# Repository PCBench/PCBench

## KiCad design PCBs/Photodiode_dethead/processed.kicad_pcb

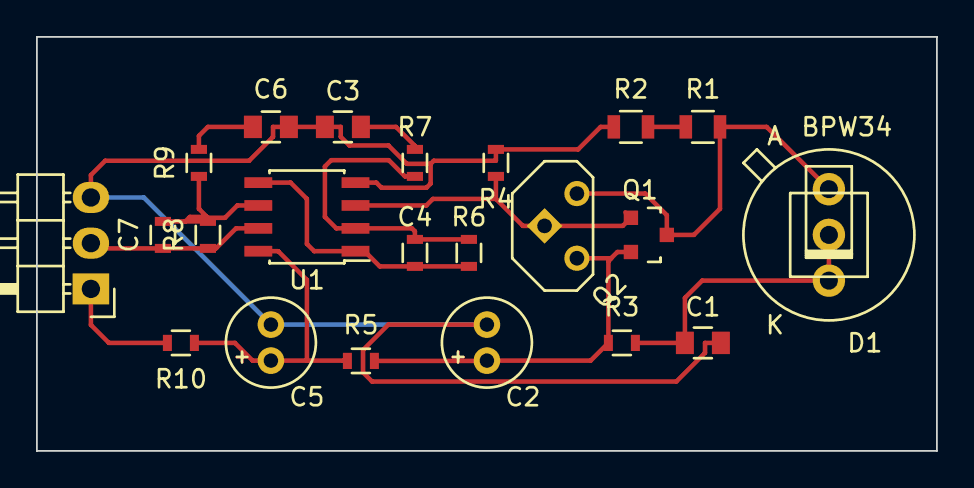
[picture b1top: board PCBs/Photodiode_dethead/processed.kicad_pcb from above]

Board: 2 copper layers, 50.0 x 23.0 mm, 22 parts (0 on the bottom side), 14 nets.

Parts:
C1, C3, C6: 100n; C_0805
C2, C5: 100u; Elko_vert_11x5mm_RM2
C4, C7: 47p; R_0603
D1: BPW34; PHOTODIODE_MULTI
P1: CONN_01X03; Pin_Header_Angled_1x03
Q1: BF545; SOT-23
Q2: FET_N; TO92GSD
R1, R2: 10M; R_0805
R3: 1M; R_0603
R4: 4k7; R_0603
R5: 1k; R_0603
R6, R8: 330k; R_0603
R7, R9: 10k; R_0603
R10: 100; R_0603
U1: LM358N; SOIC-8_3.9x4.9mm_Pitch1.27mm

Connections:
+BATT: P1.1, R10.1
/BIAS: C1.1, D1.2, R3.2
/DIODE_OUT: D1.1, Q1.3, Q2.G, R1.2
/SIG_OUT: C7.1, P1.2, R8.1, U1.7
GND: C1.2, C2.2, C3.2, C5.2, C6.2, P1.3, R2.1, R4.1, U1.4
unnamed: C2.1, Q1.2, Q2.D, R3.1, R5.2
unnamed: C3.1, R7.2
unnamed: C4.1, R6.1, U1.1, U1.5
unnamed: C4.2, R6.2, R7.1, U1.2
unnamed: C6.1, R9.2
unnamed: C7.2, R8.2, R9.1, U1.6
unnamed: Q1.1, Q2.S, R4.2, U1.3
unnamed: R1.1, R2.2
VCC: C5.1, R5.1, R10.2, U1.8

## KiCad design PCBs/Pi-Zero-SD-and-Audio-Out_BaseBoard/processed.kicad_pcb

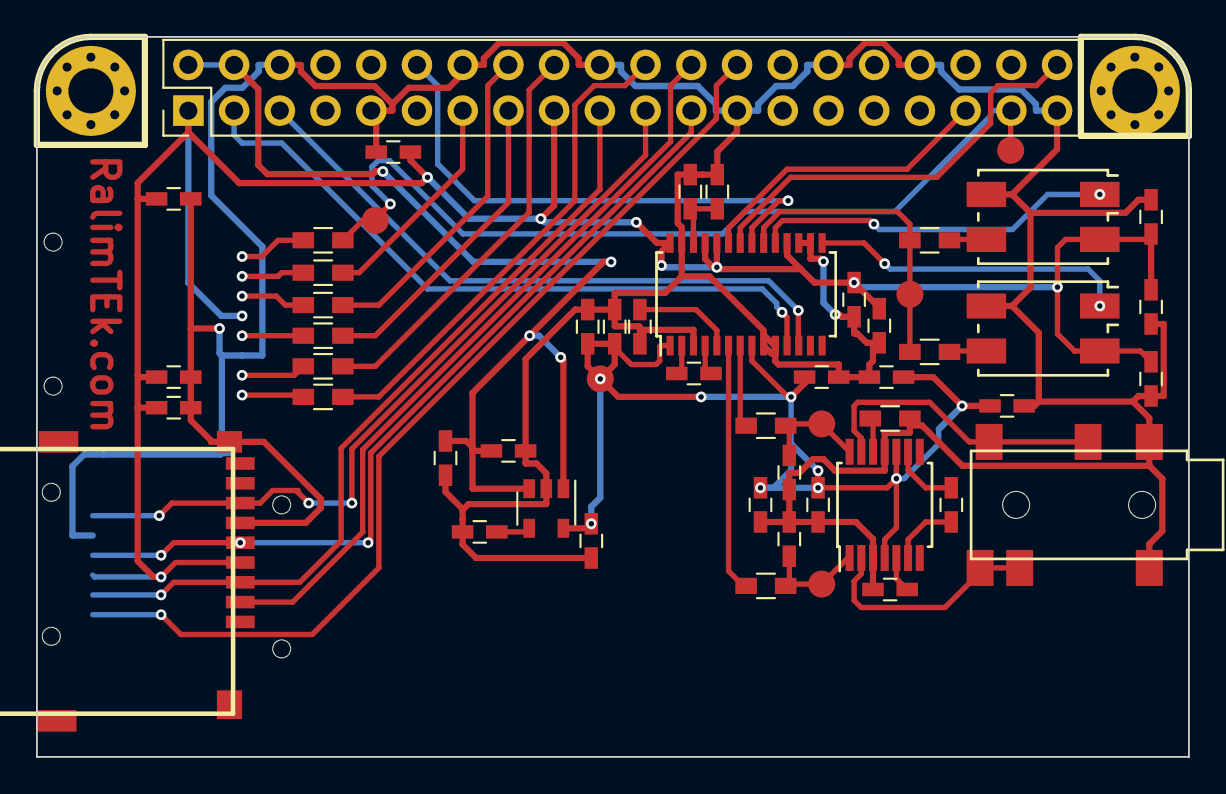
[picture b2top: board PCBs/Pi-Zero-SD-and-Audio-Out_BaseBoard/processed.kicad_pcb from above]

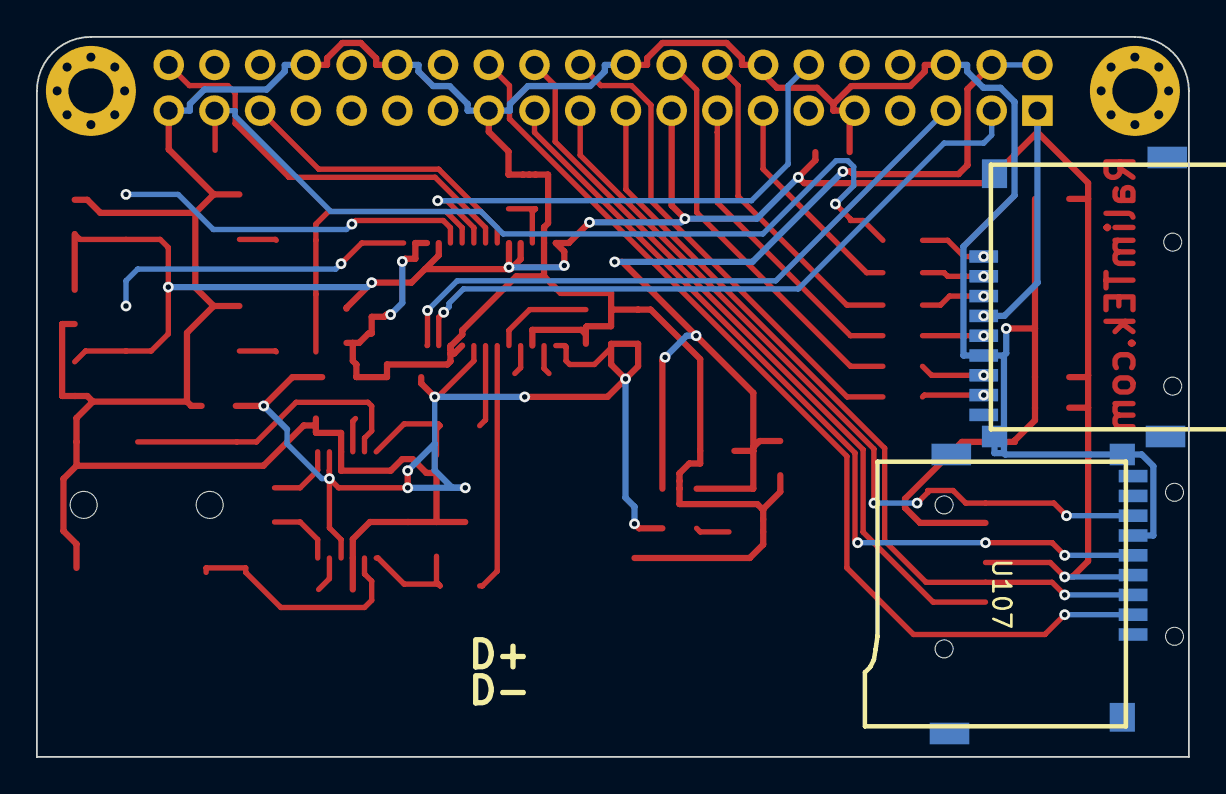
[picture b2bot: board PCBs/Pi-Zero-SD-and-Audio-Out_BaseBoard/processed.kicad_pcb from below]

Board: 2 copper layers, 64.0 x 40.0 mm, 57 parts (2 on the bottom side), 46 nets.

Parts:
C101, C102, C106, C107, C110, C111, C112, C113, C114, C115, C116, C117, C118, C119, C120, C121, C122, C123, C124, C125, C126, C127, C128: 0.1u; C_0603_HandSoldering
C103, C104, C105: 2.2uF; C_0603_HandSoldering
C108, C109: -; C_0603_HandSoldering
J101: RaspberryPi; Pin_Header_Straight_2x20_Pitch2.54mm
J102: JACK_TRS_6PINS; PJ311_6pin_3.5mm_SMD_Jack
P102, P104: CONN_01X01; MountingHole_2.5mm_Pad_Via
R101, R102, R103, R104, R107: 470; R_0603_HandSoldering
R105, R109: 33; R_0603_HandSoldering
R106, R108, R110, R111: 33R; R_0603_HandSoldering
U101: PCM5122; TSSOP-28_4.4x9.7mm_Pitch0.65mm
U103: TPA6139A2; TSSOP-14_4.4x5mm_Pitch0.65mm
U104: LD3985G; SOT-23-5
U105: Micro_SD_SDIO; GCT-MEM2055-00-190-01-A
U106, U107: MicroSD_SPI_CD; GCT-MEM2055-00-190-01-A
W101: CLK; Measurement_Point_Round-SMD-Pad_Small
W102: 3.3V; Measurement_Point_Round-SMD-Pad_Small
W103: L; Measurement_Point_Round-SMD-Pad_Small
W104: R; Measurement_Point_Round-SMD-Pad_Small
W108, W109: DAT2Link; Measurement_Point_Round-SMD-Pad_Small
X101: 24.576MHz; Crystal_SMD_7050_4Pads
X102: 22.5792MHz; Crystal_SMD_7050_4Pads

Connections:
/22MHZ_EN: U101.19, X102.1
/24MHZ_EN: U101.15, X101.1
/AVDD: C104.1, C111.1, C112.1, C113.1, C117.1, C119.1, C127.1, C128.1, U101.1, U101.8, U103.4, U103.10, U104.5, W102.1
/BCK: J101.12, U101.21
/CLK: J101.15, R105.2
/CMD: J101.16, R109.2
/DAC_L: C109.1, R101.2, U103.1, W103.1
/DAC_R: C108.2, R102.1, U103.14, W104.1
/DAT0: J101.18, R110.2
/DAT1: J101.22, R106.2
/DAT2: J101.37, R111.2, W108.1, W109.1
/DAT3: J101.13, R108.2
/DIN: J101.40, U101.22
/LRCLK: J101.35, U101.23
/MISO: J101.21, U106.7, U107.7
/MOSI: J101.19, U106.3, U107.3
/OUT_L: J102.4, J102.5, U103.2
/OUT_R: J102.3, J102.6, U103.13
/SCK: R103.2, R104.2, U101.20, W101.1
/SCL: J101.5, U101.12
/SCLK: J101.23, U106.5, U107.5
/SDA: J101.3, U101.11
/VBATT: C118.1, C120.1, J101.2, J101.4, U104.1, U104.3
/~CE0: J101.24, U106.2
/~CE1: J101.26, U107.2
GND: C101.2, C102.2, C104.2, C105.1, C106.2, C108.1, C109.2, C110.2, C111.2, C112.2, C113.2, C114.2, C115.2, C116.2, C117.2, C118.2, C119.2, C120.2, C121.2, C122.2, C123.2, C124.2, C125.2, C126.2, C127.2, C128.2, J101.6, J101.9, J101.14, J101.20, J101.25, J101.30, J101.34, J101.39, J102.1, J102.2, R107.2, U101.3, U101.9, U101.10, U101.16, U101.17, U101.27, U103.3, U103.11, U104.2, U105.6, U105.10, U106.6, U106.10, U107.6, U107.10, X101.2, X102.2
unnamed: C101.1, C102.1, U101.26
unnamed: C103.1, U101.2
unnamed: C103.2, U101.4
unnamed: C105.2, U101.5
unnamed: C106.1, U103.5
unnamed: C107.1, U103.9
unnamed: C107.2, U103.6
unnamed: C110.1, U104.4
unnamed: R101.1, U101.6
unnamed: R102.2, U101.7
unnamed: R103.1, X101.3
unnamed: R104.1, X102.3
unnamed: R105.1, U105.5
unnamed: R106.1, U105.8
unnamed: R107.1, U103.12
unnamed: R108.1, U105.2
unnamed: R109.1, U105.3
unnamed: R110.1, U105.7
unnamed: R111.1, U105.1
VDD: C114.1, C115.1, C116.1, C121.1, C122.1, C123.1, C124.1, C125.1, C126.1, J101.1, J101.17, U101.18, U101.24, U101.25, U101.28, U105.4, U106.4, U107.4, X101.4, X102.4

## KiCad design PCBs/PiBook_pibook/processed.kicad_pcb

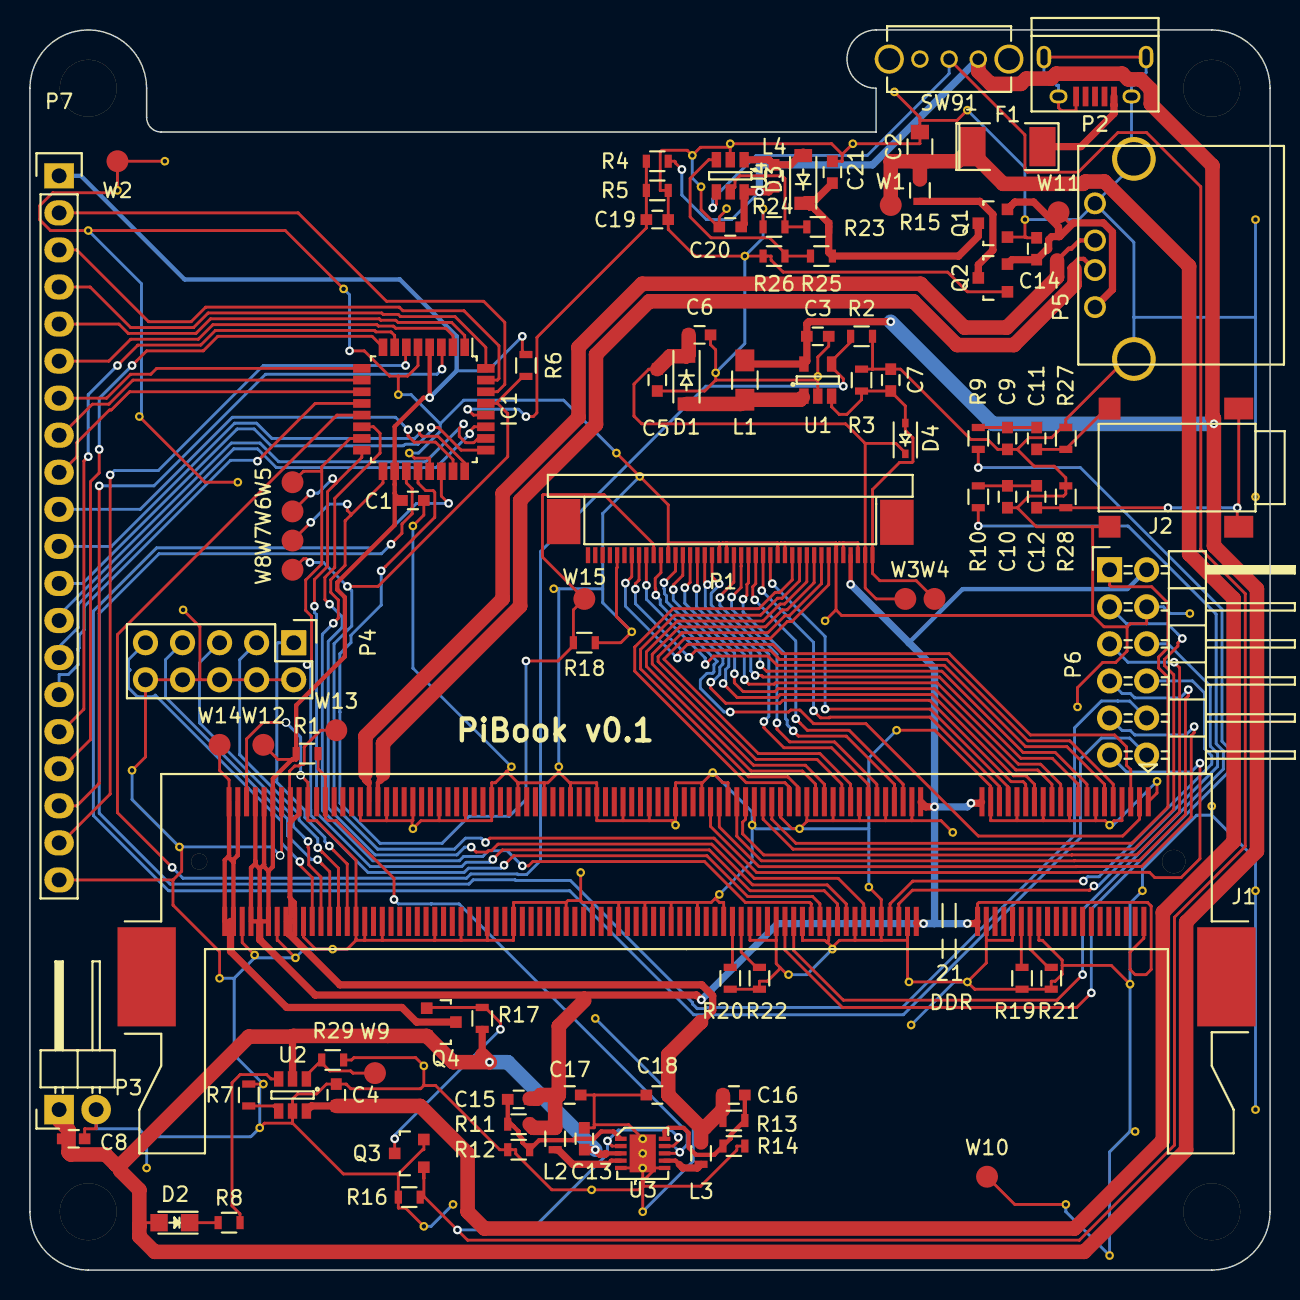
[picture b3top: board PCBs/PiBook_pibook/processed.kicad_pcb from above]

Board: 2 copper layers, 85.0 x 85.0 mm, 98 parts (0 on the bottom side), 103 nets.

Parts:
C1, C4, C5, C6, C7, C8, C11, C12, C20, C21: 1u; C_0603
C2: 22u; C_0805
C3: 4.7u; C_0603
C9, C10: 82n; C_0603
C13, C14, C17, C18: 10u; C_0603
C15, C16: 18p; C_0603
C19: 100n; C_0603
D1, D3: MBR0540T3G; SOD-123
D2: LED; LED_0805
D4: MM32Z24VT1G; SOD-323
F1: 2A; SMD-2010_Pol
IC1: ATTINY48-A; LQFP-32_7x7mm_Pitch0.8mm
J1: ComputeModule; Socket_SODIMM_DDR1-2_TE_1612618
J2: TRS_JACK_3PIN; TRS_3_SMD
L1: 6.8u; R_0805_HandSoldering
L2, L3: 2.2u; R_0603
L4: 10u; C_0603
MH1, MH2, MH3, MH4: Mounting_Hole; Mounting_hole_M3.5
P1: CONN_01X40; FPC40_BOTTOM
P2: USB_OTG; USB_Micro-B
P3: CONN_01X02; Pin_Header_Angled_1x02
P4: CONN_02X05; Pin_Header_Straight_2x05
P5: USB_A
P6: CONN_02X06; Pin_Header_Angled_2x06
P7: CONN_01X20; Pin_Header_Straight_1x20
Q1, Q2, Q4: Si2323DS; SOT-23
Q3: BSS138P; SOT-23
R1, R2, R4, R5, R6, R12, R14, R16, R17, R18, R19, R20, R21, R22, R27, R28: 100k; R_0603
R3: 12; R_0603
R7: 680; R_0603
R8: R; R_0603
R9, R10: 100; R_0603
R11: 450k; R_0603
R13: 200k; R_0603
R15: 0; R_0603
R23: 47k; R_0603
R24, R26, R29: 10k; R_0603
R25: 40k; R_0603
SW91: SPST; SPDT_SLIDE_SWITCH
TP1: Tie_point; tiepoint-0.3
U1: FAN5333; SOT-23-5
U2: BQ21040; SOT-23-6
U3: NCP1532; UDFN-10
U4: MIC2619YD6; SOT-23-6
W1: USB_VIN+; Measurement_Point_Round-SMD-Pad_Small
W2: USB_VIN-; Measurement_Point_Round-SMD-Pad_Small
W3: BACKL_A; Measurement_Point_Round-SMD-Pad_Small
W4: BACKL_K; Measurement_Point_Round-SMD-Pad_Small
W5, W6, W7, W8, W15: TEST_1P; Measurement_Point_Round-SMD-Pad_Small
W9: TS; Measurement_Point_Round-SMD-Pad_Small
W10: GND; Measurement_Point_Round-SMD-Pad_Small
W11: VUSB_OUT; Measurement_Point_Round-SMD-Pad_Small
W12: +3V3; Measurement_Point_Round-SMD-Pad_Small
W13: +1V8; Measurement_Point_Round-SMD-Pad_Small
W14: CM_VBAT; Measurement_Point_Round-SMD-Pad_Small

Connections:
+1V8: C16.1, C18.1, J1.183, J1.184, J1.185, J1.186, L3.2, R13.1, W13.1
+3V3: C1.1, C15.1, C17.1, IC1.4, IC1.18, J1.2, J1.39, J1.40, J1.41, J1.42, J1.189, J1.190, J1.191, J1.192, J1.193, J1.194, L2.2, P1.4, P6.2, P7.1, R1.1, R6.1, R11.1, W12.1
+5V: C21.1, D3.1, Q1.3, R23.1, R25.1
+BATT: C3.1, C8.1, C13.1, C20.1, D2.2, L1.1, L4.1, P3.1, Q4.2, R4.1, R17.1, SW91.1, U1.5, U2.2, U3.3, U4.6
+VUSB_IN: C2.1, C4.1, F1.1, R15.2, U2.6, W1.1
+VUSB_OUT: C14.1, P5.1, Q1.2, Q2.2, W11.1
/ANALOG0: IC1.19, P6.10
/ANALOG1: IC1.22, P6.12
/AUDIO_L_PWM: J1.70, R10.2
/AUDIO_R_PWM: J1.72, R9.2
/AVR_MISO: IC1.16, J1.60, W6.1
/AVR_MOSI: IC1.15, J1.64, W5.1
/AVR_SCK: IC1.17, J1.66, W7.1
/AVR_~CS: IC1.14, J1.58
/AVR_~RST: IC1.29, J1.54, R6.2, W8.1
/BACKL_A: C5.1, C6.1, D1.1, D4.1, P1.2, W3.1
/BACKL_K: C7.1, D4.2, P1.1, R3.1, U1.3, W4.1
/BACKL_PWM: IC1.13, R2.1, U1.4
/CM_RUN: J1.177, R1.2, U3.8
/CM_VBAT: J1.197, J1.198, J1.199, J1.200, Q4.3, W14.1
/KEY_C0: IC1.30, P7.2
/KEY_C1: IC1.31, P7.3
/KEY_C2: IC1.32, P7.4
/KEY_C3: IC1.1, P7.5
/KEY_C4: IC1.2, P7.6
/KEY_C5: IC1.9, P7.7
/KEY_C6: IC1.10, P7.8
/KEY_C7: IC1.11, P7.9
/KEY_C8: IC1.23, P7.10
/KEY_C9: IC1.24, P7.11
/KEY_C10: IC1.25, P7.12
/KEY_C11: IC1.26, P7.13
/KEY_R0: IC1.27, P7.14
/KEY_R1: IC1.12, P7.15
/KEY_R2: IC1.7, P7.16
/KEY_R3: IC1.8, P7.17
/KEY_R4: IC1.3, P7.18
/KEY_R5: IC1.6, P7.19
/LCD_B_2: J1.15, P1.23
/LCD_B_3: J1.17, P1.24
/LCD_B_4: J1.21, P1.25
/LCD_B_5: J1.23, P1.26
/LCD_B_6: J1.27, P1.27
/LCD_B_7: J1.29, P1.28
/LCD_CLK: J1.3, P1.30
/LCD_DEN: J1.5, P1.34
/LCD_DISP_ON: IC1.20, P1.31, R18.1, W15.1
/LCD_G_2: J1.33, P1.15
/LCD_G_3: J1.35, P1.16
/LCD_G_4: J1.45, P1.17
/LCD_G_5: J1.47, P1.18
/LCD_G_6: J1.51, P1.19
/LCD_G_7: J1.53, P1.20
/LCD_HSYNC: J1.11, P1.32
/LCD_R_2: J1.57, P1.7
/LCD_R_3: J1.59, P1.8
/LCD_R_4: J1.63, P1.9
/LCD_R_5: J1.65, P1.10
/LCD_R_6: J1.69, P1.11
/LCD_R_7: J1.71, P1.12
/LCD_VSYNC: J1.9, P1.33
/PWR_ENABLE: Q3.1, R16.1, SW91.2, U3.2, U3.9, U4.4
/UART_RX: J1.48, P6.8
/UART_TX: J1.46, P6.6
/USB_D+: J1.165, P5.2
/USB_D-: J1.167, P5.3
/USER_IO_0: J1.75, P6.1
/USER_IO_1: J1.77, P6.3
/USER_IO_2: J1.81, P6.5
/USER_IO_3: J1.83, P6.7
/USER_IO_4: J1.87, P6.9
/USER_IO_5: J1.89, P6.11
/VC_TCK: J1.180, P4.9
/VC_TDI: J1.174, P4.3
/VC_TDO: J1.178, P4.5
/VC_TMS: J1.176, P4.7
/VC_TRST_N: J1.172, P4.1
GND: C1.2, C2.2, C3.2, C4.2, C5.2, C6.2, C7.2, C8.2, C9.2, C10.2, C14.2, C19.2, C20.2, C21.2, IC1.5, IC1.21, J1.1, J1.7, J1.13, J1.19, J1.25, J1.26, J1.31, J1.32, J1.37, J1.38, J1.43, J1.44, J1.49, J1.50, J1.55, J1.56, J1.61, J1.62, J1.67, J1.68, J1.73, J1.74, J1.79, J1.80, J1.85, J1.86, J1.91, J1.92, J1.97, J1.98, J1.103, J1.104, J1.109, J1.110, J1.115, J1.116, J1.121, J1.122, J1.127, J1.133, J1.134, J1.139, J1.140, J1.145, J1.146, J1.151, J1.152, J1.157, J1.163, J1.164, J1.168, J1.169, J1.170, J1.181, J1.182, J1.187, J1.188, J1.195, J1.196, J2.2, P1.3, P1.5, P1.6, P1.13, P1.14, P1.21, P1.22, P1.29, P1.36, P2.5, P2.6, P3.2, P4.2, P4.4, P4.6, P4.8, P4.10, P5.4, P5.5, P6.4, P7.20, Q1.1, Q2.1, Q3.2, R2.2, R3.2, R5.2, R7.1, R12.2, R14.2, R16.2, R18.2, R19.2, R20.2, R21.2, R22.2, R24.2, R26.2, R27.2, R28.2, R29.1, TP1.2, U1.2, U2.5, U4.2, W2.1, W10.1
GNDPWR: C13.2, C17.2, C18.2, TP1.1, U3.5, U3.6
unnamed: C10.1, C12.1, R10.1
unnamed: C9.1, C11.1, R9.1
unnamed: C11.2, J2.3, R27.1
unnamed: C12.2, J2.1, R28.1
unnamed: C15.2, R11.2, R12.1, U3.1
unnamed: C16.2, R13.2, R14.1, U3.10
unnamed: C19.1, IC1.28, R4.2, R5.1
unnamed: D1.2, L1.2, U1.1
unnamed: D2.1, R8.1
unnamed: D3.2, L4.2, U4.1
unnamed: F1.2, P2.1
unnamed: J1.28, R21.1
unnamed: J1.30, R19.1
unnamed: J1.82, R22.1
unnamed: J1.84, R20.1
unnamed: L2.1, U3.4
unnamed: L3.1, U3.7
unnamed: Q2.3, R15.1
unnamed: Q3.3, Q4.1, R17.2
unnamed: R7.2, U2.4
unnamed: R8.2, U2.3
unnamed: R23.2, R24.1, U4.5
unnamed: R25.2, R26.1, U4.3
unnamed: R29.2, U2.1, W9.1

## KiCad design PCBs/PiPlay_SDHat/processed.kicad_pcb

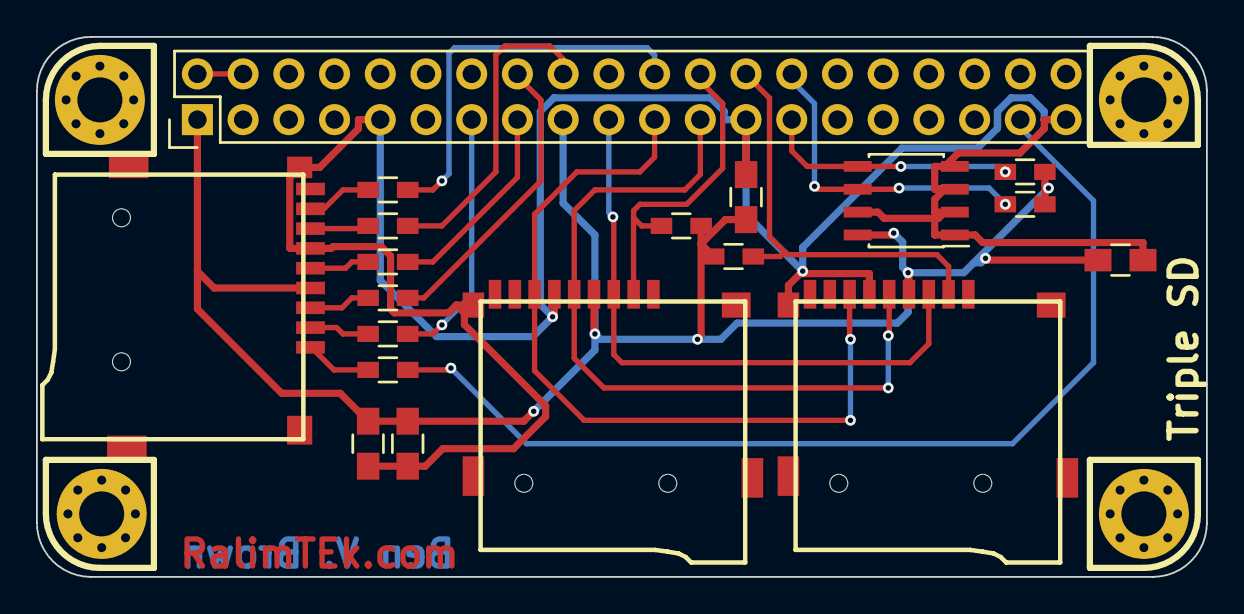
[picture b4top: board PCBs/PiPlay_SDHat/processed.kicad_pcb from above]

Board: 2 copper layers, 65.0 x 30.0 mm, 23 parts (0 on the bottom side), 22 nets.

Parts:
C101, C111, C112, C113: 0.1u; C_0805_HandSoldering
J101: RaspberryPi; Pin_Header_Straight_2x20
P101, P102, P103, P104: CONN_01X01; MountingHole_2.5mm_Pad_Via
R101, R102, R103, R104, R107, R108: 33; R_0603_HandSoldering
R105, R106, R109, R110: 4k; R_0603_HandSoldering
U101, U103: MicroSD_SPI_CD; GCT-MEM2055-00-190-01-A
U102: 24C16; SOIC-8_3.9x4.9mm_Pitch1.27mm
U104: Micro_SD_SDIO; GCT-MEM2055-00-190-01-A

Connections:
/CLK: J101.15, R102.1
/CMD: J101.16, R101.1
/CS0: J101.24, R109.2, U101.2
/CS1: J101.26, R110.2, U103.2
/DAT0: J101.18, R103.1
/DAT1: J101.22, R104.1
/DAT2: J101.37, R107.1
/DAT3: J101.13, R108.1
/ID_SCL: J101.28, R106.1, U102.6
/ID_SDA: J101.27, R105.1, U102.5
/MISO: J101.21, U101.7, U103.7
/MOSI: J101.19, U101.3, U103.3
/SCLK: J101.23, U101.5, U103.5
GND: C101.2, C111.2, C112.2, C113.2, J101.9, J101.25, J101.39, U101.6, U101.10, U102.1, U102.2, U102.3, U102.4, U102.7, U103.6, U103.10, U104.6, U104.10
unnamed: R101.2, U104.3
unnamed: R102.2, U104.5
unnamed: R103.2, U104.7
unnamed: R104.2, U104.8
unnamed: R107.2, U104.1
unnamed: R108.2, U104.2
VCC: J101.2, J101.4
VDD: C101.1, C111.1, C112.1, C113.1, J101.1, J101.17, R105.2, R106.2, R109.1, R110.1, U101.4, U102.8, U103.4, U104.4

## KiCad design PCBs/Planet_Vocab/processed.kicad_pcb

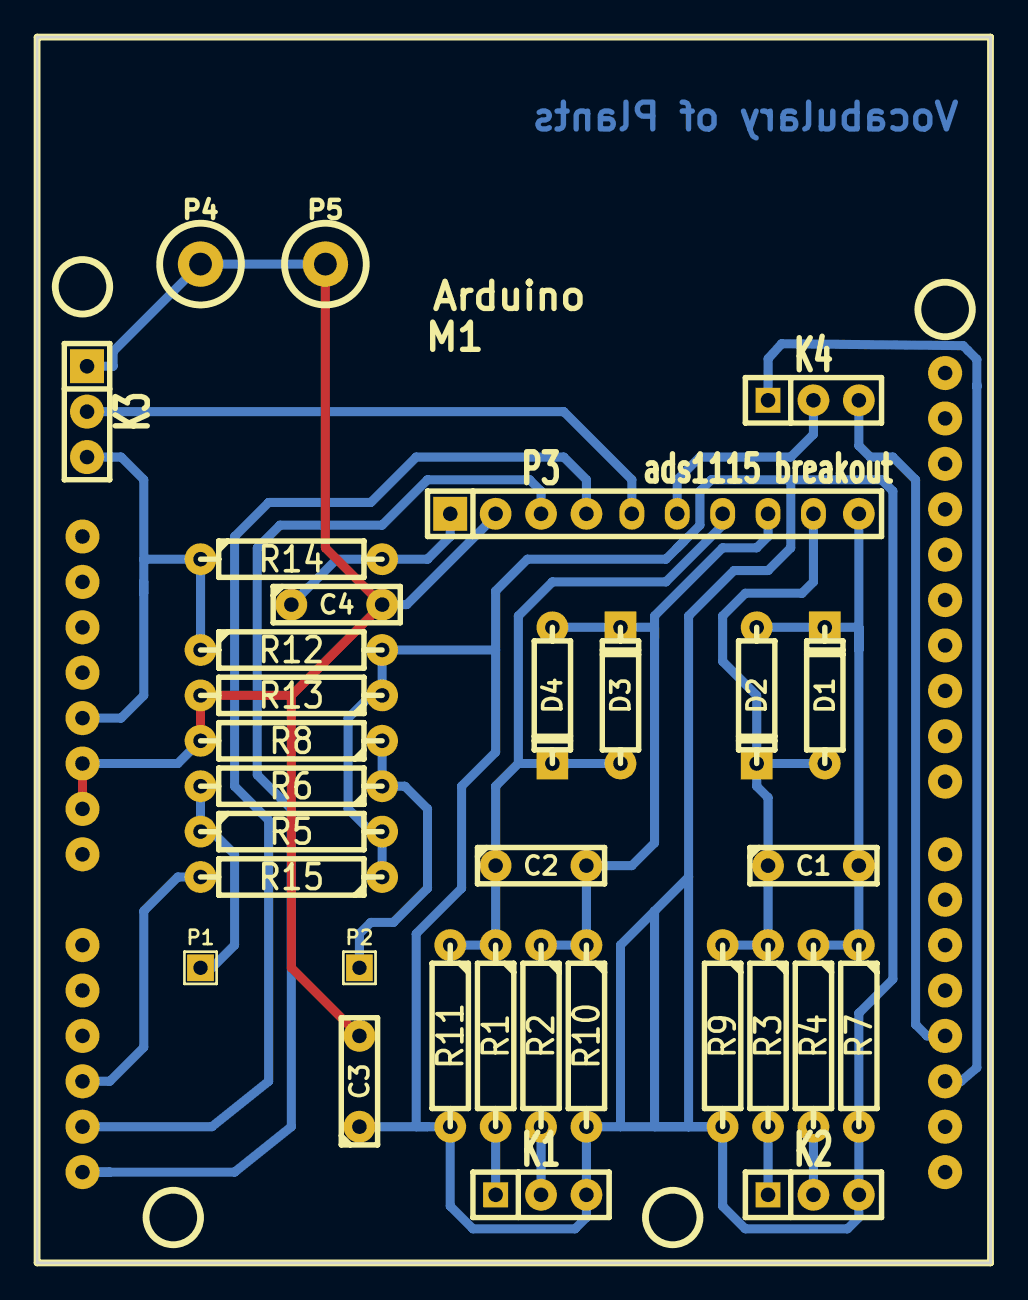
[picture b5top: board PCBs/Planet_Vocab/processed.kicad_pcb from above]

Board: 2 copper layers, 53.3 x 68.6 mm, 33 parts (0 on the bottom side), 21 nets.

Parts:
C1, C2: 100n; C2
C3, C4: 10u; C2
D1, D2, D3, D4: 1n914; D3
K1, K2, K3, K4: CONN_3; SIL-3
M1: Arduino
P1, P2: CONN_1; SIL-1
P3: ads1115 breakout; SIL-10
P4, P5: CONN_1; 1pin
R1, R2, R3, R4: 100K; R4-LARGE_PADS
R5, R12, R13, R15: 10k; R4-LARGE_PADS
R6: 100k; R4-LARGE_PADS
R7, R8, R9, R10, R11: 1M; R4-LARGE_PADS
R14: 0R; R4-LARGE_PADS

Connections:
+5V: K3.3, M1.3, R12.1, R14.1
GND: C3.2, C4.2, K3.1, M1.4, M1.5, P3.2, P4.1, P5.1, R8.2, R13.2
unnamed: C2.1, D3.1, D4.2, P3.7, R1.1, R11.1
unnamed: M1.12, P3.3
unnamed: M1.11, P3.4
unnamed: C4.1, P3.1, R14.2
unnamed: M1.10, R15.2
unnamed: K4.2, P3.6
unnamed: P2.1, R6.1, R8.1
unnamed: P1.1, R5.1, R6.2
unnamed: K4.1, M1.15
unnamed: K4.3, M1.16
unnamed: K3.2, P3.5
unnamed: C2.2, D3.2, D4.1, P3.8, R2.1, R10.1
unnamed: K1.1, R1.2
unnamed: K1.2, R2.2
unnamed: K2.1, R3.2
unnamed: K2.2, R4.2
unnamed: C3.1, K1.3, K2.3, R5.2, R7.2, R9.2, R10.2, R11.2, R12.2, R13.1, R15.1
unnamed: C1.1, D1.1, D2.2, P3.9, R3.1, R9.1
unnamed: C1.2, D1.2, D2.1, P3.10, R4.1, R7.1

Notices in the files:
PCBs/Pi-Zero-SD-and-Audio-Out_BaseBoard/processed.kicad_pcb:
License: CERN OHL V1.2
